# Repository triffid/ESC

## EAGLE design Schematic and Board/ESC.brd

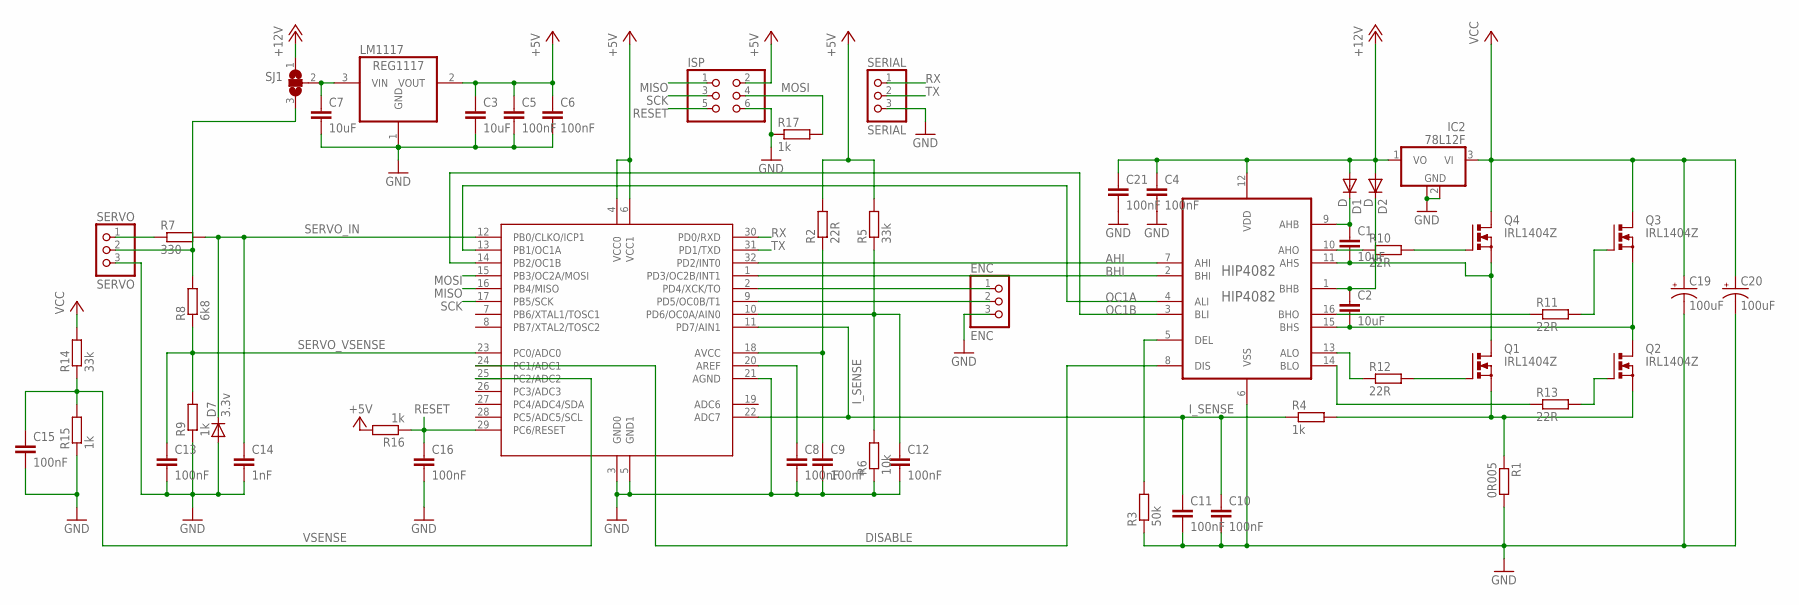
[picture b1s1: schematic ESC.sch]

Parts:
ATMEGA328: ATMEGA328; MLF32
C1, C2, C3, C7: 10uF; C0805K
C4, C5, C6, C8, C9, C10, C11, C12, C13, C15, C16, C21: 100nF; C0603K
C14: 1nF; C0603K
C19, C20: 100uF; PANASONIC_D
D1, D2: D; SOD110-R
D7: 3.3v; SOD-123_MINI-SMA
ENC: ENC; 1X03
HIP4082: HIP4082; SOIC127P600X175-16N
IC2: 78L12F; SOT89
ISP: PINHD-2X3; 2X03
LM1117: REG1117; SOT223
Q1, Q2, Q3, Q4: IRL1404Z; TO220BV
R1: 0R005; R2512
R2, R10, R11, R12, R13: 22R; R0603
R3: 50k; R0603
R4, R9, R15, R16, R17: 1k; R0603
R5, R14: 33k; R0603
R6: 10k; R0603
R7: 330; R0805
R8: 6k8; R0603
SERIAL: SERIAL; 1X03
SERVO: SERVO; 1X03
SJ1: SJ2W; SJ_2

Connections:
+5V: ATMEGA328.4 (VCC0), ATMEGA328.6 (VCC1), C3.1, C5.1, C6.1, ISP.2, LM1117.2 (VOUT), R2.2, R5.2, R16.2
+12V: C4.1, C21.1, D1.A, D2.A, HIP4082.12 (VDD), IC2.1 (VO), SJ1.1
AHI: ATMEGA328.32 (PD2/INT0), HIP4082.7 (AHI)
BHI: ATMEGA328.1 (PD3/OC2B/INT1), HIP4082.2 (BHI)
DISABLE: ATMEGA328.24 (PC1/ADC1), HIP4082.8 (DIS)
GND: ATMEGA328.3 (GND0), ATMEGA328.5 (GND1), ATMEGA328.21 (AGND), C3.2, C4.2, C5.2, C6.2, C7.2, C8.2, C9.2, C10.2, C11.2, C12.2, C13.2, C14.2, C15.2, C16.2, C19.-, C20.-, C21.2, D7.A, ENC.3, HIP4082.6 (VSS), IC2.2 (GND), IC2.2@1 (GND), ISP.6, LM1117.1 (GND), R1.2, R3.1, R6.1, R9.1, R15.1, R17.1, SERIAL.3, SERVO.3
I_SENSE: ATMEGA328.11 (PD7/AIN1), ATMEGA328.22 (ADC7), C10.1, C11.1, R4.1
MISO: ATMEGA328.16 (PB4/MISO), ISP.1
MOSI: ATMEGA328.15 (PB3/OC2A/MOSI), ISP.4, R17.2
MO_A: C1.2, HIP4082.11 (AHS), Q1.D, Q4.S
MO_B: C2.2, HIP4082.15 (BHS), Q2.D, Q3.S
unnamed: HIP4082.14 (BLO), R13.1
unnamed: HIP4082.13 (ALO), R12.1
unnamed: HIP4082.5 (DEL), R3.2
unnamed: Q4.G, R10.2
unnamed: HIP4082.10 (AHO), R10.1
unnamed: C1.1, D1.C, HIP4082.9 (AHB)
unnamed: C2.1, D2.C, HIP4082.1 (BHB)
unnamed: ATMEGA328.18 (AVCC), C9.1, R2.1
unnamed: HIP4082.16 (BHO), R11.1
unnamed: ATMEGA328.20 (AREF), C8.1
unnamed: ATMEGA328.10 (PD6/OC0A/AIN0), C12.1, R5.1, R6.2
unnamed: Q3.G, R11.2
unnamed: R7.1, SERVO.1
unnamed: R8.2, SERVO.2, SJ1.3
unnamed: Q1.G, R12.2
unnamed: ATMEGA328.2 (PD4/XCK/TO), ENC.1
unnamed: Q2.G, R13.2
unnamed: C7.1, LM1117.3 (VIN), SJ1.2
unnamed: ATMEGA328.9 (PD5/OC0B/T1), ENC.2
OC1A: ATMEGA328.13 (PB1/OC1A), HIP4082.4 (ALI)
OC1B: ATMEGA328.14 (PB2/OC1B), HIP4082.3 (BLI)
RESET: ATMEGA328.29 (PC6/RESET), C16.1, ISP.5, R16.1
RX: ATMEGA328.30 (PD0/RXD), SERIAL.1
SCK: ATMEGA328.17 (PB5/SCK), ISP.3
SENSE: Q1.S, Q2.S, R1.1, R4.2
SERVO_IN: ATMEGA328.12 (PB0/CLKO/ICP1), C14.1, D7.C, R7.2
SERVO_VSENSE: ATMEGA328.23 (PC0/ADC0), C13.1, R8.1, R9.2
TX: ATMEGA328.31 (PD1/TXD), SERIAL.2
VCC: C19.+, C20.+, IC2.3 (VI), Q3.D, Q4.D, R14.2
VSENSE: ATMEGA328.25 (PC2/ADC2), C15.1, R14.1, R15.2

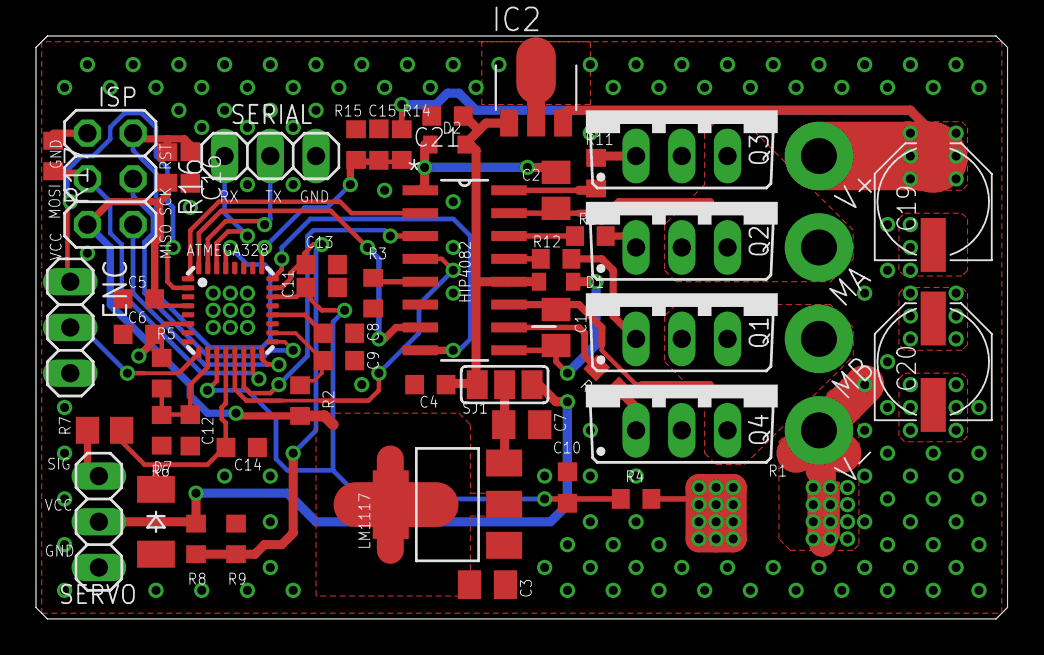
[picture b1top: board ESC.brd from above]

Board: 2 copper layers, 54.0 x 32.4 mm, 52 parts (0 on the bottom side), 41 nets.

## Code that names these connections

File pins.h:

#ifndef _PINS_H
#define _PINS_H

#define SERVO_IN	PB0

#define SERIAL_TX	PD1
#define SERIAL_RX	PD0

// #define MOSI			PB3
// #define MISO			PB4
// #define SCK				PB5

#define ENC_P0		PD4
#define ENC_P1		PD5

#define AHI			PD2
#define ALO			PB1
#define BHI			PD3
#define BLO			PB2

#define DISABLE		PC1

// analog pins!
#define SERVO_VSENSE	0
#define	MOTOR_VSENSE	2
#define ISENSE			7

#define AIN0			PD6
#define	AIN1			PD7

#endif /* _PINS_H */

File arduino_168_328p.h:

// UART
#define	RXD					DIO0
#define	TXD					DIO1

// SPI
#define	SCK					DIO13
#define	MISO				DIO12
#define	MOSI				DIO11
#define	SS					DIO10

// TWI (I2C)
#define	SCL					AIO5
#define	SDA					AIO4

// timers and PWM
#define	OC0A				DIO6
#define	OC0B				DIO5
#define	OC1A				DIO9
#define	OC1B				DIO10
#define	OC2A				DIO11
#define	OC2B				DIO3

#define	DEBUG_LED			DIO13

/*
pins
*/

#define DIO0_PIN		PIND0
#define DIO0_RPORT	PIND
#define DIO0_WPORT	PORTD
#define DIO0_DDR		DDRD
#define DIO0_PWM		NULL

#define DIO1_PIN		PIND1
#define DIO1_RPORT	PIND
#define DIO1_WPORT	PORTD
#define DIO1_DDR		DDRD
#define DIO1_PWM		NULL

#define DIO2_PIN		PIND2
#define DIO2_RPORT	PIND
#define DIO2_WPORT	PORTD
#define DIO2_DDR		DDRD
#define DIO2_PWM		NULL

#define DIO3_PIN		PIND3
#define DIO3_RPORT	PIND
#define DIO3_WPORT	PORTD
#define DIO3_DDR		DDRD
#define DIO3_PWM		&OCR2B

#define DIO4_PIN		PIND4
#define DIO4_RPORT	PIND
#define DIO4_WPORT	PORTD
#define DIO4_DDR		DDRD
#define DIO4_PWM		NULL

#define DIO5_PIN		PIND5
#define DIO5_RPORT	PIND
#define DIO5_WPORT	PORTD
#define DIO5_DDR		DDRD
#define DIO5_PWM		&OCR0B

#define DIO6_PIN		PIND6
#define DIO6_RPORT	PIND
#define DIO6_WPORT	PORTD
#define DIO6_DDR		DDRD
#define DIO6_PWM		&OCR0A

#define DIO7_PIN		PIND7
#define DIO7_RPORT	PIND
#define DIO7_WPORT	PORTD
#define DIO7_DDR		DDRD
#define DIO7_PWM		NULL

#define DIO8_PIN		PINB0
#define DIO8_RPORT	PINB
#define DIO8_WPORT	PORTB
#define DIO8_DDR		DDRB
#define DIO8_PWM		NULL

#define DIO9_PIN		PINB1
#define DIO9_RPORT	PINB
#define DIO9_WPORT	PORTB
#define DIO9_DDR		DDRB
#define DIO9_PWM		&OCR1A

#define DIO10_PIN		PINB2
#define DIO10_RPORT	PINB
#define DIO10_WPORT	PORTB
#define DIO10_DDR		DDRB
#define DIO10_PWM		&OCR1B

#define DIO11_PIN		PINB3
#define DIO11_RPORT	PINB
#define DIO11_WPORT	PORTB
#define DIO11_DDR		DDRB
#define DIO11_PWM		&OCR2A

#define DIO12_PIN		PINB4
#define DIO12_RPORT	PINB
#define DIO12_WPORT	PORTB
#define DIO12_DDR		DDRB
#define DIO12_PWM		NULL

#define DIO13_PIN		PINB5
#define DIO13_RPORT	PINB
#define DIO13_WPORT	PORTB
#define DIO13_DDR		DDRB
#define DIO13_PWM		NULL


#define AIO0_PIN		PINC0
#define AIO0_RPORT	PINC
#define AIO0_WPORT	PORTC
#define AIO0_DDR		DDRC
#define AIO0_PWM		NULL

#define AIO1_PIN		PINC1
#define AIO1_RPORT	PINC
#define AIO1_WPORT	PORTC
#define AIO1_DDR		DDRC
#define AIO1_PWM		NULL

#define AIO2_PIN		PINC2
#define AIO2_RPORT	PINC
#define AIO2_WPORT	PORTC
#define AIO2_DDR		DDRC
#define AIO2_PWM		NULL

#define AIO3_PIN		PINC3
#define AIO3_RPORT	PINC
#define AIO3_WPORT	PORTC
#define AIO3_DDR		DDRC
#define AIO3_PWM		NULL

#define AIO4_PIN		PINC4
#define AIO4_RPORT	PINC
#define AIO4_WPORT	PORTC
#define AIO4_DDR		DDRC
#define AIO4_PWM		NULL

#define AIO5_PIN		PINC5
#define AIO5_RPORT	PINC
#define AIO5_WPORT	PORTC
#define AIO5_DDR		DDRC
#define AIO5_PWM		NULL

#define AIO6_PIN		6

#define AIO7_PIN		7



#undef PB0
#define PB0_PIN			PINB0
#define PB0_RPORT		PINB
#define PB0_WPORT		PORTB
#define PB0_DDR			DDRB
#define PB0_PWM			NULL

#undef PB1
#define PB1_PIN			PINB1
#define PB1_RPORT		PINB
#define PB1_WPORT		PORTB
#define PB1_DDR			DDRB
#define PB1_PWM			&OCR1A

#undef PB2
#define PB2_PIN			PINB2
#define PB2_RPORT		PINB
#define PB2_WPORT		PORTB
#define PB2_DDR			DDRB
#define PB2_PWM			&OCR1B

#undef PB3
#define PB3_PIN			PINB3
#define PB3_RPORT		PINB
#define PB3_WPORT		PORTB
#define PB3_DDR			DDRB
#define PB3_PWM			&OCR2A

#undef PB4
#define PB4_PIN			PINB4
#define PB4_RPORT		PINB
#define PB4_WPORT		PORTB
#define PB4_DDR			DDRB
#define PB4_PWM			NULL

#undef PB5
#define PB5_PIN			PINB5
#define PB5_RPORT		PINB
#define PB5_WPORT		PORTB
#define PB5_DDR			DDRB
#define PB5_PWM			NULL

#undef PB6
#define PB6_PIN			PINB6
#define PB6_RPORT		PINB
#define PB6_WPORT		PORTB
#define PB6_DDR			DDRB
#define PB6_PWM			NULL

#undef PB7
#define PB7_PIN			PINB7
#define PB7_RPORT		PINB
#define PB7_WPORT		PORTB
#define PB7_DDR			DDRB
#define PB7_PWM			NULL


#undef PC0
#define PC0_PIN			PINC0
#define PC0_RPORT		PINC
#define PC0_WPORT		PORTC
#define PC0_DDR			DDRC
#define PC0_PWM			NULL

#undef PC1
#define PC1_PIN			PINC1
#define PC1_RPORT		PINC
#define PC1_WPORT		PORTC
#define PC1_DDR			DDRC
#define PC1_PWM			NULL

#undef PC2
#define PC2_PIN			PINC2
#define PC2_RPORT		PINC
#define PC2_WPORT		PORTC
#define PC2_DDR			DDRC
#define PC2_PWM			NULL

#undef PC3
#define PC3_PIN			PINC3
#define PC3_RPORT		PINC
#define PC3_WPORT		PORTC
#define PC3_DDR			DDRC
#define PC3_PWM			NULL

#undef PC4
#define PC4_PIN			PINC4
#define PC4_RPORT		PINC
#define PC4_WPORT		PORTC
#define PC4_DDR			DDRC
#define PC4_PWM			NULL

#undef PC5
#define PC5_PIN			PINC5
#define PC5_RPORT		PINC
#define PC5_WPORT		PORTC
#define PC5_DDR			DDRC
#define PC5_PWM			NULL

#undef PC6
#define PC6_PIN			PINC6
#define PC6_RPORT		PINC
#define PC6_WPORT		PORTC
#define PC6_DDR			DDRC
#define PC6_PWM			NULL

#undef PC7
#define PC7_PIN			PINC7
#define PC7_RPORT		PINC
#define PC7_WPORT		PORTC
#define PC7_DDR			DDRC
#define PC7_PWM			NULL


#undef PD0
#define PD0_PIN			PIND0
#define PD0_RPORT		PIND
#define PD0_WPORT		PORTD
#define PD0_DDR			DDRD
#define PD0_PWM			NULL

#undef PD1
#define PD1_PIN			PIND1
#define PD1_RPORT		PIND
#define PD1_WPORT		PORTD
#define PD1_DDR			DDRD
#define PD1_PWM			NULL

#undef PD2
#define PD2_PIN			PIND2
#define PD2_RPORT		PIND
#define PD2_WPORT		PORTD
#define PD2_DDR			DDRD
#define PD2_PWM			NULL

#undef PD3
#define PD3_PIN			PIND3
#define PD3_RPORT		PIND
#define PD3_WPORT		PORTD
#define PD3_DDR			DDRD
#define PD3_PWM			&OCR2B

#undef PD4
#define PD4_PIN			PIND4
#define PD4_RPORT		PIND
#define PD4_WPORT		PORTD
#define PD4_DDR			DDRD
#define PD4_PWM			NULL

#undef PD5
#define PD5_PIN			PIND5
#define PD5_RPORT		PIND
#define PD5_WPORT		PORTD
#define PD5_DDR			DDRD
#define PD5_PWM			&OCR0B

#undef PD6
#define PD6_PIN			PIND6
#define PD6_RPORT		PIND
#define PD6_WPORT		PORTD
#define PD6_DDR			DDRD
#define PD6_PWM			&OCR0A

#undef PD7
#define PD7_PIN			PIND7
#define PD7_RPORT		PIND
#define PD7_WPORT		PORTD
#define PD7_DDR			DDRD
#define PD7_PWM			NULL

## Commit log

2012-11-18 initial commit: PCB design
2012-11-18 updated board: makes better use of PWM outputs, also adds optional ACS712 hall effect current sensor
2012-11-18 ESC Firmware: working on altered versions of initial board design, should in theory work on current board design
2012-11-18 added some comments in config.h
2012-11-18 move some debug stuff around for first release
2012-11-18 add lots of comments, license, headers in a few files. also remove redundant stuff from esc.c
2012-11-20 fix race condition around use of ADC results
2014-12-03 24V adaption - add 7812, expand board, add VMM capacitors, add encoder input.
2014-12-03 solve potential race condition on servo_pulse_width, update gitignore
2014-12-03 Minor tidying
2014-12-03 More board tweaks
2014-12-03 Remove ACS712, improve ground stitching and layout
